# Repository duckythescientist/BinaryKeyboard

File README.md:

# BinaryKeyboard
1 and 0 are the only keys a true programmer needs

Now with Unicode support! 

[Youtube](https://youtu.be/qHAFpK-0hug) and [Youtube](https://www.youtube.com/watch?v=DmWm68NnIkk)

[Gifycat](https://gfycat.com/SophisticatedWeepyButterfly)

[Imgur Album](http://imgur.com/a/icKnR)

In a fit of inspiration, I threw this together in an evening. It is a small keyboard with three keys: `0`, `1`, and `enter/submit`.

Unicode support happened a separate day. 

## Functionality

### Mode 0
The `0` key types a "0". The `1` key types a "1". The `enter/submit` key types the enter key.

### Mode 1
This is the true binary mode. To type an ASCII letter, press a combination of 8 `0`s and `1`s (MSB first) then press `enter/submit`. If you press `enter/submit` with greater or fewer than 8 bits, this clears all of the bits. This allows you to clear screwups without having any letters actually typed. 

### NEW: Unicode Hybrid Mode (1)
As a modification to "Mode 1", you can now enter Unicode characters!!! Instead of just typing 8 bits, type anywhere from 3 to 8 nibbles before pressing `enter/submit`. Typing exactly 8 bits will fallback to the standard Mode 1.

[Gifv](https://i.imgur.com/321nCg8.gifv)

For Linux, the keyboard uses a modification of the CTRL+SHIFT+U method. It has been tested with Debian Jessie (Xfce) and partially tested with Ubuntu 14.04 (Unity).

For Windows, the keyboard uses the ALT+NUMPAD_PLUS hexadecimal method. This requires a registry edit. To `HKEY_CURRENT_USER\Control Panel\Input Method` add a string (`REG_SZ`) called `EnableHexNumpad` with the value `1` then reboot. Unfortunately, Windows doesn't seem to like anything more than 4 nibbles with this method. There are other methods, but this is the most universal for Windows. I'm very open to suggestions for ways to fix this. 

## Mode Selection:
When plugging in the USB cable, the keyboard will startup and default to Mode 0, QWERTY, Linux. 
* To switch to Mode 1, hold the `0` key when plugging in the keyboard. 
* To switch to Dvorak, hold `1` when plugging in the keyboard. 
* To switch to Windows Unicode mode, hold the `enter/submit` key when plugging in the keyboard. 

Key(s) must be held for around 7 seconds (dependent mostly on AUTO_EXIT_MS defined in the Micronucleus bootloader). 

## Construction
The body of the keyboard is 3D printed. Mine was done with a Monoprice Select Mini, but it's a small and forgiving design, so just about any printer should work.

The 4 keyswitches should be Cherry MX style. I'm using Gateron Blues. The 2u keycap needs double stems. This could be changed to fit a single stem or triple stem with stabilizers 2u keycap if the OpenSCAD files are changed. 

The controller is a "tinyDev" board of my creation. Order it from [PCBS.io](https://pcbs.io/share/8Dmor) or from [OSH Park](https://oshpark.com/shared_projects/nc7kkKFu) or elsewhere. Both PCBS.io and OSH Park are super cheap for small boards. 

The keyswitches share a common ground on one pin. The other pin connects directly to pins on the tinyDev. `0` to B1, `1` to B2, and `enter/submit` to B0. This can be easily changed in the code. 

Place the keyswitches in the top panel, solder the switches to the tinyDev, place the tinyDev into the base (add a little hot glue to keep it in place), and fit the top panel to the base (should be a snug press fit, if not, use glue). 

## Programming
The attiny85 on the tinyDev comes blank from the factory, so an ICSP such as the USB-ASP is needed to initially program it with the bootloader. A SOIC test clip helps immensely. The bootloader can be found [here](https://github.com/micronucleus/micronucleus). You may need/want to use the one that ships with the Digispark Arduino installation. 

Install the [Digispark boardstuffs](https://digistump.com/wiki/digispark/tutorials/connecting) to Arduino.

## BOM
Resistors and capacitors are generic 0805

2x 68ohm

1x 1.5kohm

1x 100nF

The two diodes are 3.6V zeners in a SOD-323F package. I used MM3Z3V6CCT-ND

The attiny is ATTINY85-20SURCT-ND

USB connector is Amphenol 10118194-0001LF (609-4618-1-ND on Digikey)

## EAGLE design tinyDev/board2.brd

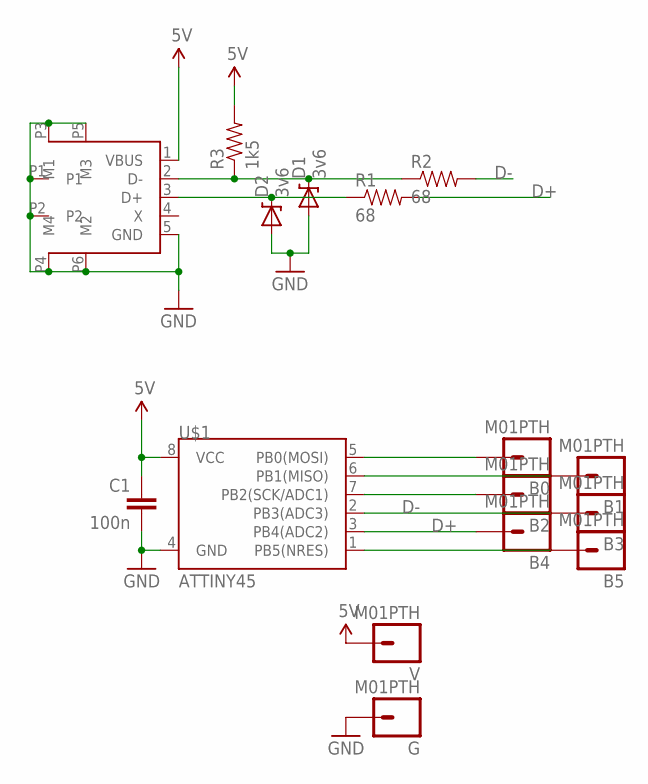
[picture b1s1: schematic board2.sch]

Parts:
B0, B1, B2, B3, B4, B5: M01PTH; 1X01
C1: 100n; 0805
CON1: USBMICRO-FCI; USBMINIB-10118194-0001LF
D1, D2: 3v6; SOD-323
G: M01PTH; 1X01
R1, R2: 68; 0805
R3: 1k5; 0805
U$1: ATTINY45; SO08-EIAJ
V: M01PTH; 1X01

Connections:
5V: C1.1, CON1.1 (VBUS), R3.2, U$1.8 (VCC), V.1
D+: B4.1, R1.2, U$1.3 (PB4(ADC2))
D-: B3.1, R2.2, U$1.2 (PB3(ADC3))
GND: C1.2, CON1.5 (GND), CON1.P1, CON1.P2, CON1.P3 (M1), CON1.P4 (M4), CON1.P5 (M3), CON1.P6 (M2), D1.2 (A), D2.2 (A), G.1, U$1.4 (GND)
unnamed: B0.1, U$1.5 (PB0(MOSI))
unnamed: B1.1, U$1.6 (PB1(MISO))
unnamed: B2.1, U$1.7 (PB2(SCK/ADC1))
unnamed: B5.1, U$1.1 (PB5(NRES))
unnamed: CON1.2 (D-), D1.1 (C), R2.1, R3.1
unnamed: CON1.3 (D+), D2.1 (C), R1.1

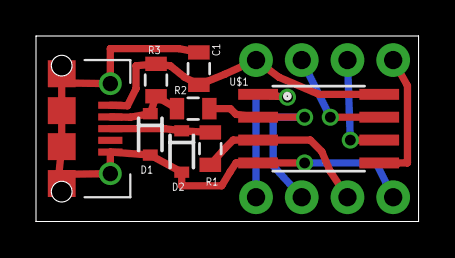
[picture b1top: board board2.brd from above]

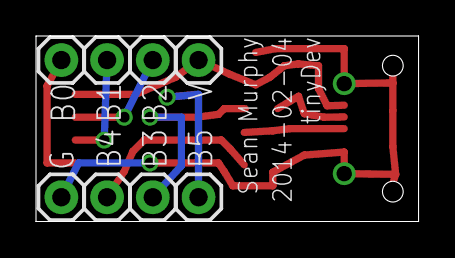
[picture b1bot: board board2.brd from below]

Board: 2 copper layers, 21.3 x 10.3 mm, 16 parts (8 on the bottom side), 10 nets.

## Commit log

2016-06-26 Add basic information to README
2016-06-26 Add case scad and stls
2016-06-26 Add Arduino code
2016-06-26 Add Dvorak patched Digikeyboard files
2016-06-26 Add board files
2016-06-26 Add youtube link to README
2016-06-26 Add image and video links to README
2016-07-17 Make Unicode work for Linux and Windows
2016-07-17 Add Unicode pics to readme
2016-07-17 Fix readme images
2019-07-17 Fixes some typos
2021-03-17 Update readme with BOM

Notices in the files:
parts and their libraries:
SparkFun-DigitalIC: Licensing: CC v3.0 Share-Alike You are welcome to use this library for commercial purposes.
